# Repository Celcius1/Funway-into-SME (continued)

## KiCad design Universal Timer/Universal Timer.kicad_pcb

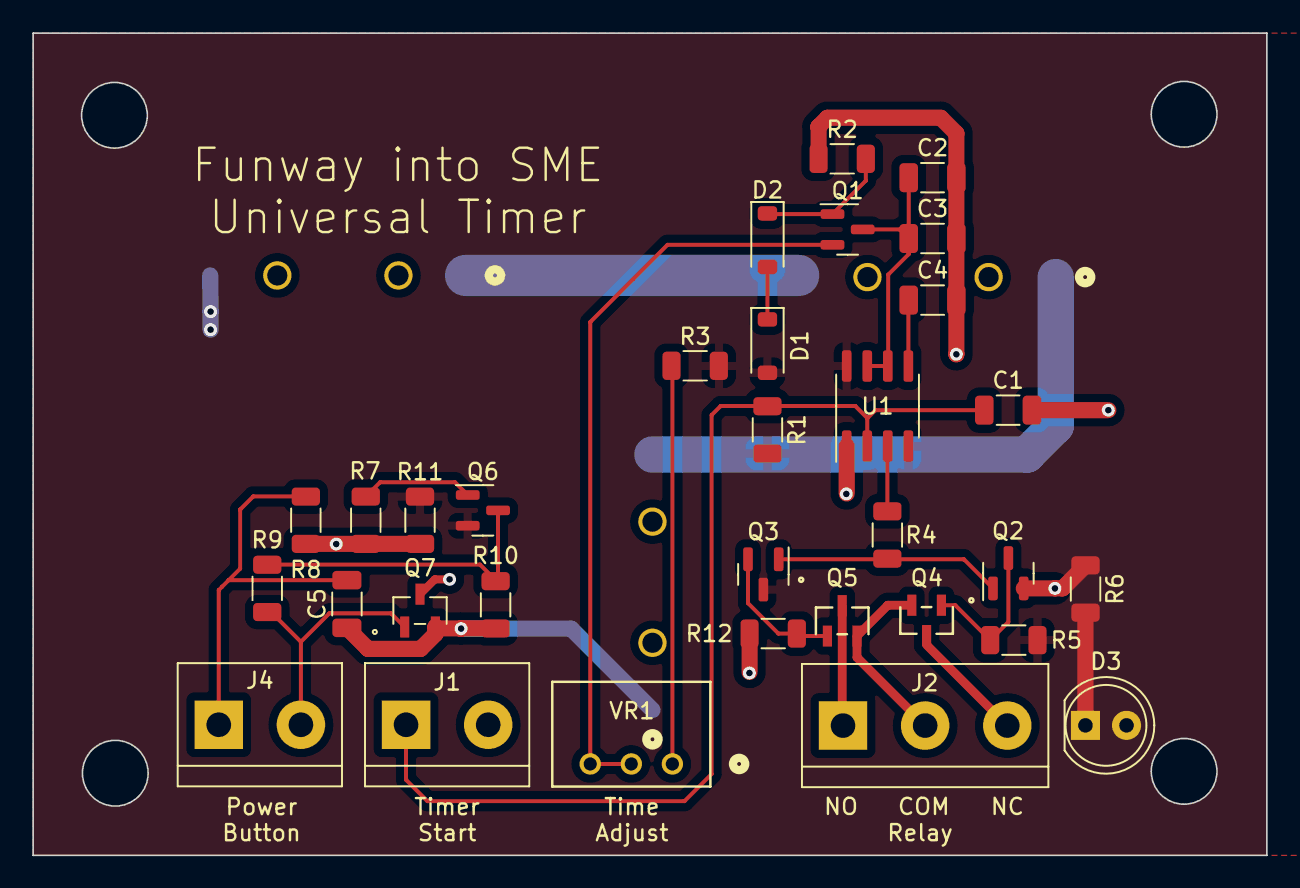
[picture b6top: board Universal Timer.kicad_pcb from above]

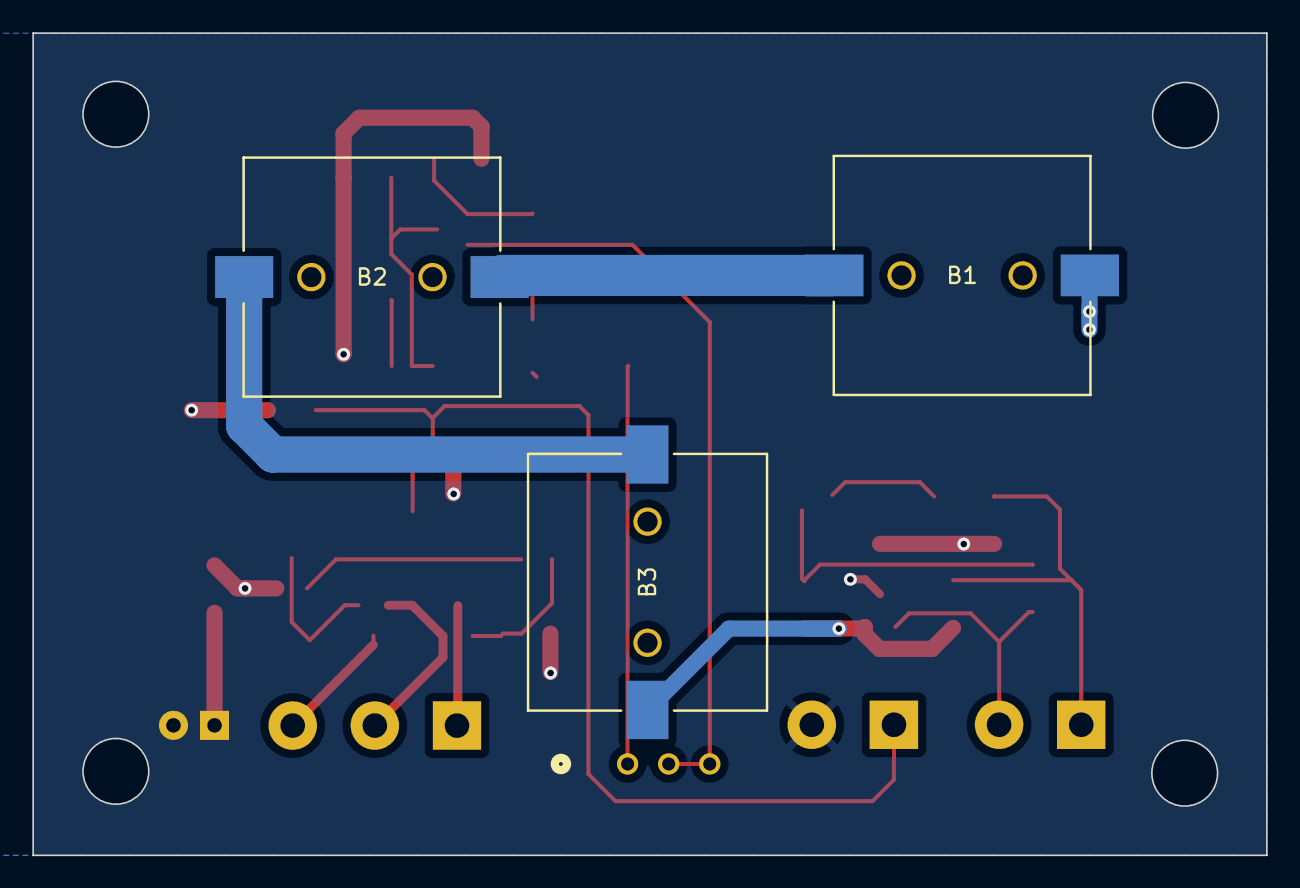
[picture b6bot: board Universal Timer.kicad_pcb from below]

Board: 2 copper layers, 76.3 x 50.9 mm, 35 parts (3 on the bottom side), 24 nets.

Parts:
B1, B2, B3: 1056TR; 1048P_KEY
C1, C4: .01uF; C_1206_3216Metric
C2, C3: 47uF; C_1206_3216Metric
C5: 330nF-1206-50V-10%; C_1206_3216Metric
D1, D2: 1N4448W; D_SOD-123
D3: LD271; LED_D5.0mm_IRGrey
J1: Timer Start; TerminalBlock_bornier-2_P5.08mm
J2: Relay Out; TerminalBlock_bornier-3_P5.08mm
J4: On/Off; TerminalBlock_bornier-2_P5.08mm
Q1, Q6: BC858; SOT-23
Q2, Q3: BC848; SOT-23
Q4, Q5: DMN2004K-7; SOT23_DIO
Q7: SI2338DS; SI2342DS-T1-GE3
R1, R4, R5, R9, R10, R11, R12: 10k; R_1206_3216Metric
R2: 6k8; R_1206_3216Metric
R3: 47k; R_1206_3216Metric
R6: 360R; R_1206_3216Metric
R7: 100k; R_1206_3216Metric
R8: 1M; R_1206_3216Metric
U1: NE555D; SOIC-8_3.9x4.9mm_P1.27mm
VR1: 1 Meg; IC3_3310C-001-105L_BRN

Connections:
9V: B1.2, D1.2 (A), D3.2 (A), Q3.3 (C), Q6.2 (E), R1.2, R3.2, R5.2, R11.2, U1.4 (R), U1.8 (VCC)
CRTGND: C1.2, C2.2, C3.2, C4.2, J1.2, Q2.2 (E), Q7.3, R2.1, R6.1, R7.1, R8.2, R11.1, R12.1, U1.1 (GND)
GND: B3.1, C5.1, Q7.2, R10.1
unnamed: B1.1, B2.2
unnamed: B2.1, B3.2
unnamed: D1.1 (K), D2.2 (A)
unnamed: D2.1 (K), Q1.1 (B), R2.2
unnamed: D3.1 (K), R6.2
unnamed: C1.1, J1.1, R1.1, U1.2 (TR)
unnamed: J2.1, Q5.3 (D)
unnamed: J2.2, Q4.2 (S), Q5.2 (S)
unnamed: J2.3, Q4.3 (D)
unnamed: C5.2, J4.1, R8.1
unnamed: J4.2, Q7.1, R9.1
unnamed: C2.1, C3.1, Q1.3 (C), U1.6 (THR), U1.7 (DIS)
unnamed: Q1.2 (E), VR1.2 (WIPER), VR1.3 (CW)
unnamed: Q2.1 (B), Q3.1 (B), R4.2
unnamed: Q2.3 (C), Q4.1 (G), R5.1
unnamed: Q3.2 (E), Q5.1 (G), R12.2
unnamed: Q6.1 (B), R7.2
unnamed: Q6.3 (C), R9.2, R10.2
unnamed: C4.1, U1.5 (CV)
unnamed: R4.1, U1.3 (Q)
unnamed: R3.1, VR1.1 (CCW)

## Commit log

2023-07-21 Completed LED Flasher Project
2023-07-21 Ding Dong Doorbell Project
2023-07-23 Universal Timer
2023-07-24 Backups Update
2023-09-30 Updates and improvements to LED Flasher
2023-09-30 Fixed Silkscreen
2023-10-03 Some Updates
2023-10-14 Morse Code Trainer
2023-10-15 Electronic Dice Projects
2023-10-15 Quick Update
2023-10-22 Completed Monophonic Organ Board
2023-10-27 Fixed mistake on organ pcb
